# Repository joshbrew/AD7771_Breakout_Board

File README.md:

# AD7771_Breakout_Board
Unfinished AD7771 Breakout design. It works it's just not final.

The flex pieces were just unfinished thought experiments on a quick and dirty way to implement these AD7771 boards for FNIRS.

The board designs do work, but the Isolated DC-DC converter pin declarations in the schematics are backwards, found out the hard way so it is fixed in the design just not the footprint names in the .sch

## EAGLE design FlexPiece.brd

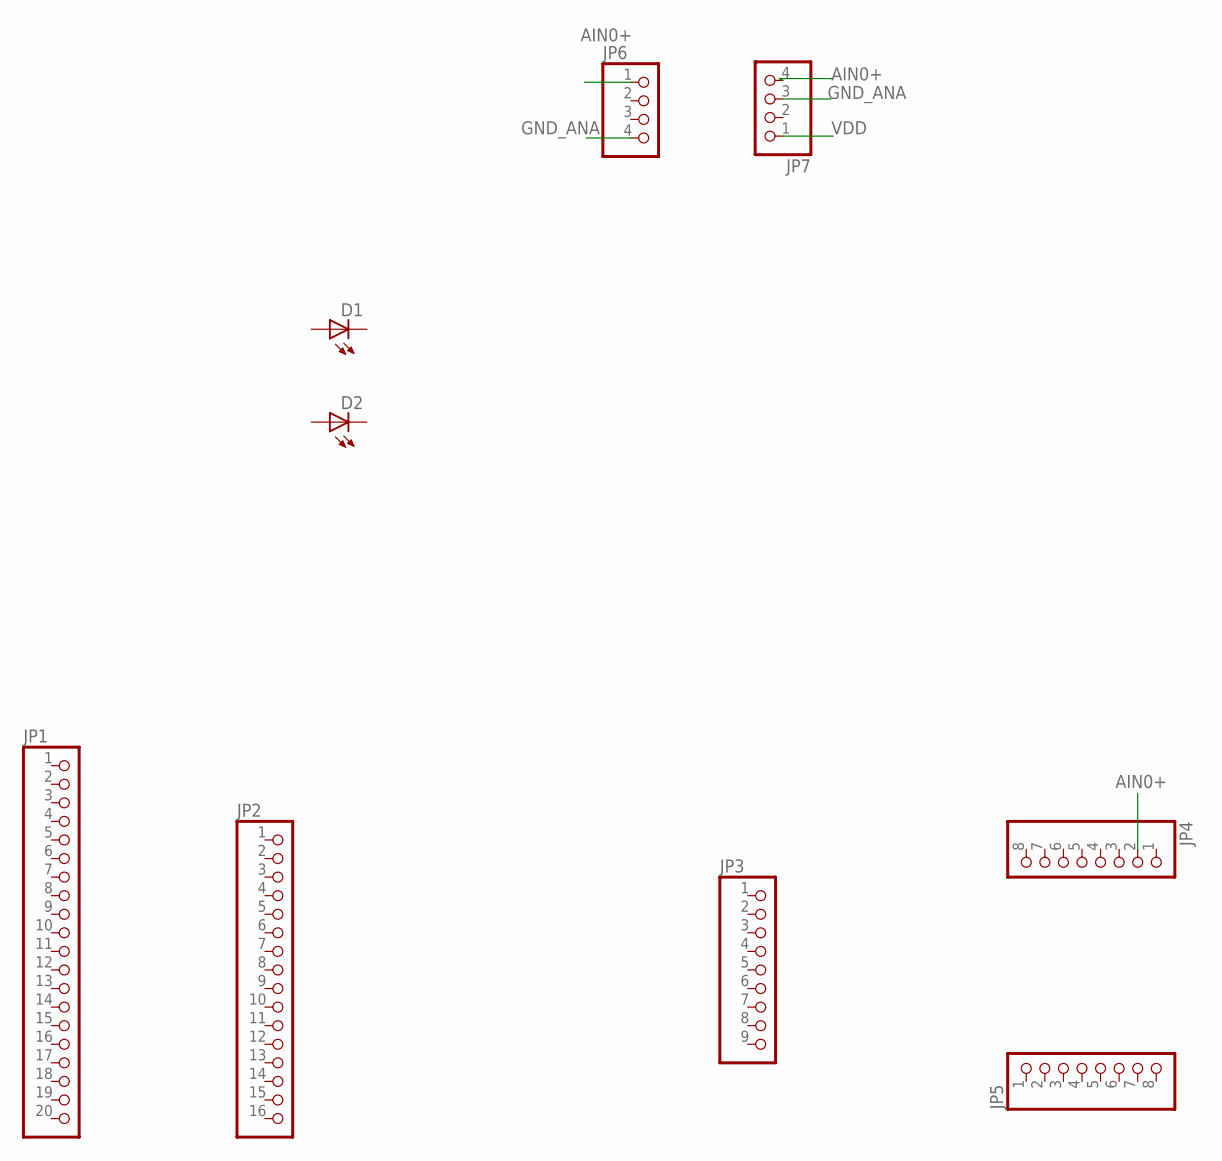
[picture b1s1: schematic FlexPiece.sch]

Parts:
D1, D2: LED1206; LED-1206
JP1: PINHD-1X20; 1X20
JP2: PINHD-1X16; 1X16
JP3: PINHD-1X9; 1X09
JP4, JP5: PINHD-1X8; 1X08
JP6, JP7: PINHD-1X4; 1X04

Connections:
AIN0+: JP4.2, JP6.1, JP7.4
GND_ANA: JP6.4, JP7.3
VDD: JP7.1

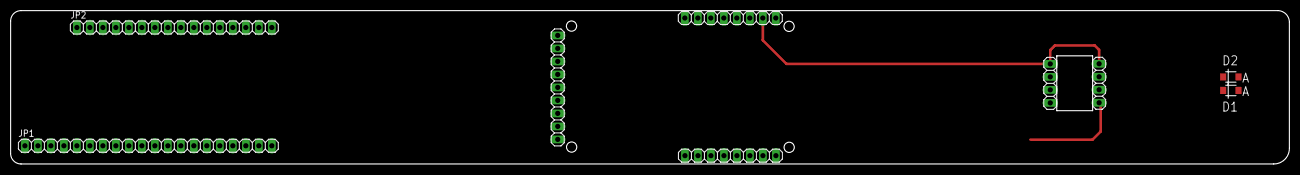
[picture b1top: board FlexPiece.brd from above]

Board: 2 copper layers, 249.9 x 30.0 mm, 9 parts (0 on the bottom side), 2 nets.

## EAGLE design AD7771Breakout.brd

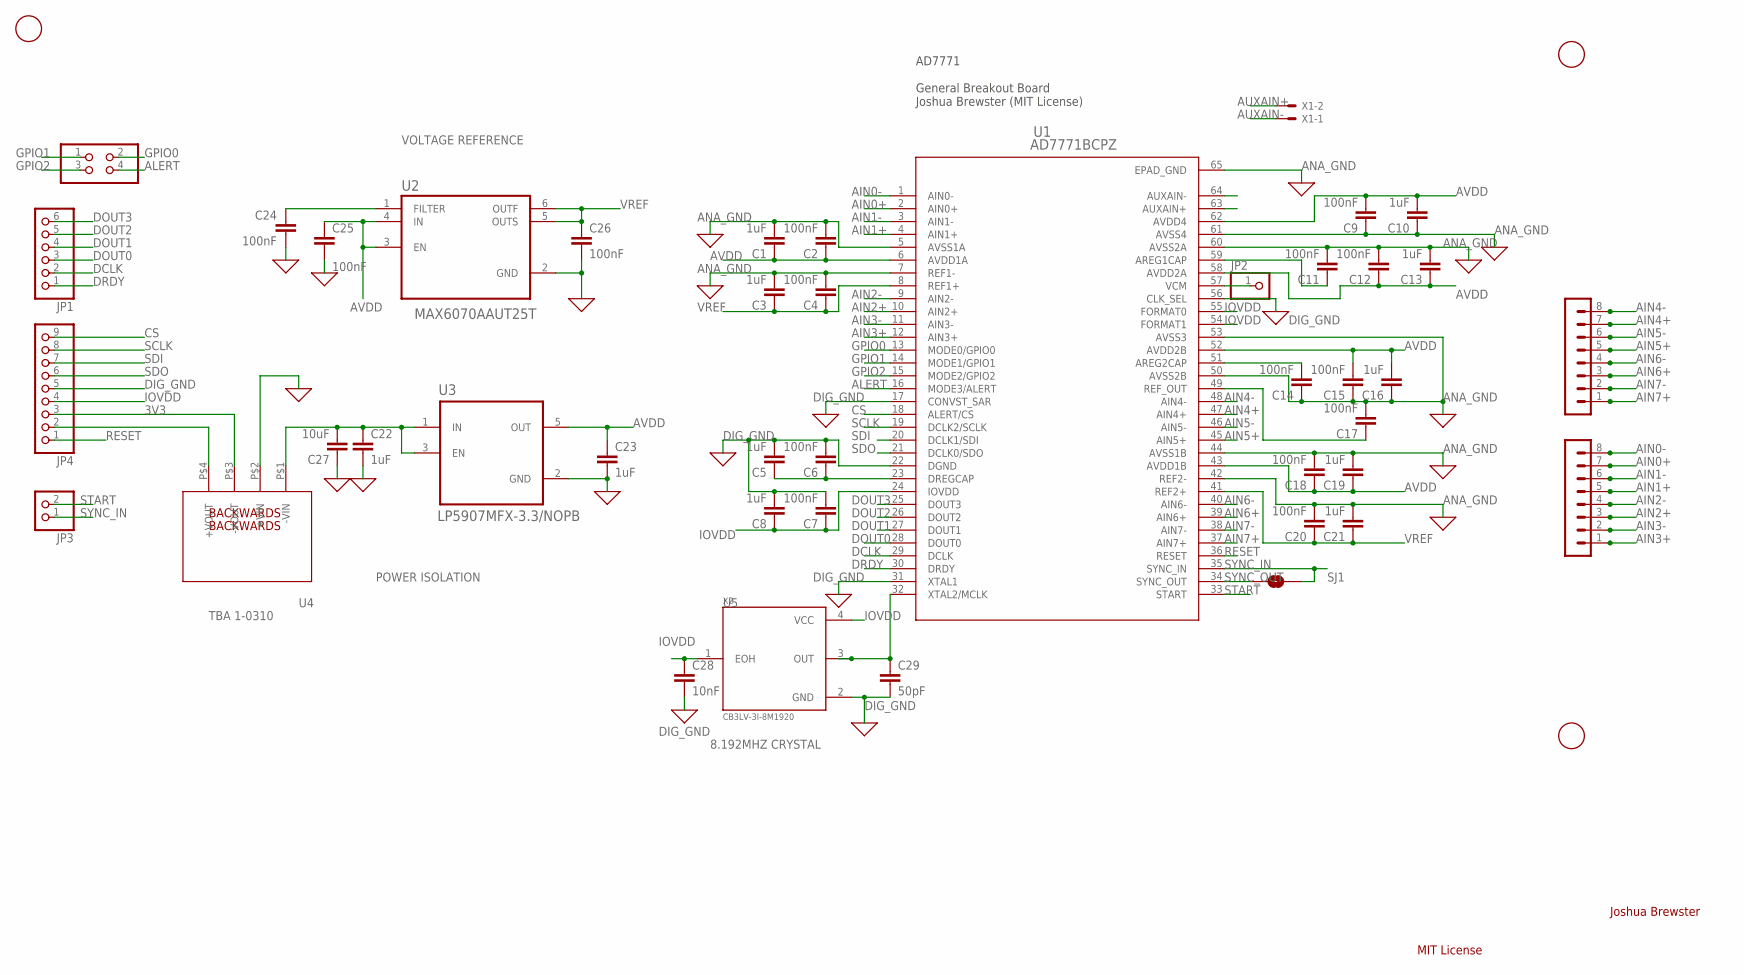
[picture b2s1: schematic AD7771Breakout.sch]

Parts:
C1, C3, C5, C8, C10, C13, C16, C19, C21, C22, C23: 1uF; C0402
C2, C4, C6, C7, C9, C11, C12, C14, C15, C17, C18, C20, C24, C25, C26: 100nF; C0402
C27: 10uF; C0402
C28: 10nF; C0402
C29: 50pF; C0603
JP1: PINHD-1X6; 1X06
JP2: PINHD-1X1; 1X01
JP3: PINHD-1X2; 1X02
JP4: PINHD-1X9; 1X09
JP5: PINHD-2X2; 2X02
SJ1: SOLDERJUMPERNC; SJ_2S_SMALL
SV4, SV5: MA08-1
U1: AD7771BCPZ; CP_64_15_ADI
U2: MAX6070AAUT25T; SOT95P280X145-6N
U3: LP5907MFX-3.3/NOPB; SOT95P280X145-5N
U4: TBA1-0310; SIP4-KT
U$1, U$2, U$5: FIDUCIAL; FIDUCIAL_1MM
X1: 332-02
X2: CB3LV-3I-8M1920; OSCCC700X500X180-4N

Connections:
3V3: JP4.3, U4.P$3 (-VOUT)
AGND_OUT: JP4.2, U4.P$4 (+VOUT)
AIN0+: SV4.7, U1.2 (AIN0+)
AIN0-: SV4.8, U1.1 (AIN0-)
AIN1+: SV4.5, U1.4 (AIN1+)
AIN1-: SV4.6, U1.3 (AIN1-)
AIN2+: SV4.3, U1.10 (AIN2+)
AIN2-: SV4.4, U1.9 (AIN2-)
AIN3+: SV4.1, U1.12 (AIN3+)
AIN3-: SV4.2, U1.11 (AIN3-)
AIN4+: SV5.7, U1.47 (AIN4+)
AIN4-: SV5.8, U1.48 (AIN4-)
AIN5+: SV5.5, U1.45 (AIN5+)
AIN5-: SV5.6, U1.46 (AIN5-)
AIN6+: SV5.3, U1.39 (AIN6+)
AIN6-: SV5.4, U1.40 (AIN6-)
AIN7+: SV5.1, U1.37 (AIN7+)
AIN7-: SV5.2, U1.38 (AIN7-)
ALERT: JP5.4, U1.16 (MODE3/ALERT)
ANA_GND: C1.2, C2.2, C3.2, C4.2, C9.1, C10.1, C11.2, C12.2, C13.2, C14.1, C15.1, C16.1, C17.2, C18.2, C19.2, C20.2, C21.2, C22.2, C23.2, C24.2, C25.2, C26.2, C27.1, U1.5 (AVSS1A), U1.7 (REF1-), U1.42 (REF2-), U1.44 (AVSS1B), U1.50 (AVSS2B), U1.53 (AVSS3), U1.60 (AVSS2A), U1.61 (AVSS4), U1.65 (EPAD_GND), U2.2 (GND), U3.2 (GND), U4.P$2 (+VIN)
AREG1CAP: C11.1, U1.59 (AREG1CAP)
AREG2CAP: C14.2, U1.51 (AREG2CAP)
AUXAIN+: U1.63 (AUXAIN+), X1.2
AUXAIN-: U1.64 (AUXAIN-), X1.1
AVDD: C1.1, C2.1, C9.2, C10.2, C12.1, C13.1, C15.2, C16.2, C18.1, C19.1, C23.1, C25.1, U1.6 (AVDD1A), U1.43 (AVDD1B), U1.52 (AVDD2B), U1.58 (AVDD2A), U1.62 (AVDD4), U2.3 (EN), U2.4 (IN), U3.5 (OUT)
CS: JP4.9, U1.18 (ALERT/CS)
DCLK: JP1.2, U1.29 (DCLK)
DIG_GND: C5.2, C6.2, C7.2, C8.2, C28.2, C29.2, JP4.5, U1.17 (CONVST_SAR), U1.22 (DGND), U1.31 (XTAL1), U1.56 (CLK_SEL), X2.2 (GND)
DOUT0: JP1.3, U1.28 (DOUT0)
DOUT1: JP1.4, U1.27 (DOUT1)
DOUT2: JP1.5, U1.26 (DOUT2)
DOUT3: JP1.6, U1.25 (DOUT3)
DRDY: JP1.1, U1.30 (DRDY)
DREGCAP: C5.1, C6.1, U1.23 (DREGCAP)
FILTER: C24.1, U2.1 (FILTER)
GPIO0: JP5.2, U1.13 (MODE0/GPIO0)
GPIO1: JP5.1, U1.14 (MODE1/GPIO1)
GPIO2: JP5.3, U1.15 (MODE2/GPIO2)
IOVDD: C7.1, C8.1, C28.1, JP4.4, U1.24 (IOVDD), U1.54 (FORMAT1), U1.55 (FORMAT0), X2.1 (EOH), X2.4 (VCC)
REF_OUT: C17.1, U1.49 (REF_OUT)
RESET: JP4.1, U1.36 (RESET)
SCLK: JP4.8, U1.19 (DCLK2/SCLK)
SDI: JP4.7, U1.20 (DCLK1/SDI)
SDO: JP4.6, U1.21 (DCLK0/SDO)
START: JP3.2, U1.33 (START)
SYNC_IN: JP3.1, SJ1.2, U1.35 (SYNC_IN)
SYNC_OUT: SJ1.1, U1.34 (SYNC_OUT)
VCM: JP2.1, U1.57 (VCM)
VOUT+: C22.1, C27.2, U3.1 (IN), U3.3 (EN), U4.P$1 (-VIN)
VREF: C3.1, C4.1, C20.1, C21.1, C26.1, U1.8 (REF1+), U1.41 (REF2+), U2.5 (OUTS), U2.6 (OUTF)
XTAL2: C29.1, U1.32 (XTAL2/MCLK), X2.3 (OUT)

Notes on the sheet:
AD7771 General Breakout Board Joshua Brewster (MIT License)
TBA 1-0310
POWER ISOLATION
VOLTAGE REFERENCE
8.192MHZ CRYSTAL
Joshua Brewster
MIT License
BACKWARDS

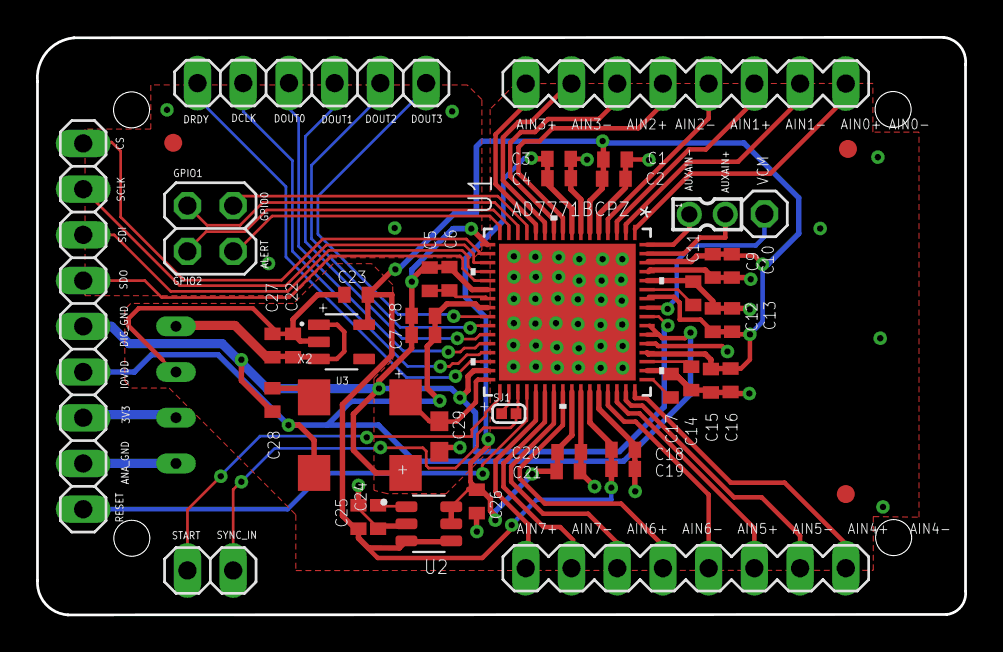
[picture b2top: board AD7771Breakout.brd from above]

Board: 2 copper layers, 51.6 x 32.1 mm, 46 parts (1 on the bottom side), 51 nets.

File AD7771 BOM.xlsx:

Designation | Qty | Package | Value | Part # | Mouser Prices (high) | 1.0 | 10.0 | 100.0 | 1000.0 | Link
U1 | 1.0 |  |  | AD7771BCPZ | 584-AD7771BCPZ | 18.23 | 167.5 | 1345.0 | 11360.0 | https://www.mouser.com/ProductDetail/Analog-Devices/AD7771BC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
U2 | 1.0 |  |  | MAX6070AAUT25T | 700-MAX6070AAUT25+T | 2.63 | 23.6 | 183.0 | 1600.0 | https://www.mouser.com/ProductDetail/Maxim-Integrated/MAX607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
U3 | 1.0 |  |  | LP5907MFX-3.3/NOPB | 595-LP5907MFX-3.3NPB | 0.55 | 4.31 | 32.0 | 191.0 | https://www.mouser.com/ProductDetail/Texas-Instruments/LP590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
U4 | 1.0 |  |  | TBA 1-0310 | 495-TBA1-0310 | 3.24 | 31.7 | 280.0 | 2430.0 | https://www.mouser.com/ProductDetail/TRACO-Power/TBA-1-0310?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
U5 | 1.0 |  |  | SG-210STF8.1920ML3 | 732-SG210STF8.1920L3 | 1.18 | 10.9 | 93.3 | 764.0 | https://www.mouser.com/ProductDetail/Epson-Timing/SG-210STF-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
C1, C3, C5, C8, C10, C13, C16, C19, C21, C22, C23 | 11.0 | C0402 | 1uF |  | 963-JMK105BJ105KP-F | 1.1 | 4.95 | 35.2 | 275 | https://www.mouser.com/ProductDetail/Taiyo-Yuden/JMK105BJ105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
C2, C4, C6, C7, C9, C11, C12, C14, C15, C17, C18, C20, C24, C25, C26 | 14.0 | C0402 | 100nF |  | 963-LMF105B7104KVHF | 1.4 | 4.2 | 28 | 182 | https://www.mouser.com/ProductDetail/Taiyo-Yuden/LMF105B7104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
C27 | 1.0 | C0402 | 10uF |  | 963-JMK105CBJ106MV-F | 0.22 | 1.02 | 8.0 | 51.0
 |  |  |  | via PCBway: | PCB Estimate (lead-free) | 18.0 | 18.0 | 50.0 | 235.0 | HASL lead free, 27mmX46.5mm, 2mm thick, any finish
 |  |  |  |  | Assembly Estimate | 88.0 | 88.0 | 232.0 | 520.0
 |  |  |  |  | Totals | 134.55 | 354.18 | 2286.5 | 17608
 |  |  |  | Additional Flex Piece Parts
 |  |  |  | OPT 101 |  | 0.9 | 9.0 | 90.0 | 900.0 | Aliexpress estimate
 |  |  |  | BR1102W |  | 0.5 | 3.09 | 14.2 | 119.0 | https://www.mouser.com/ProductDetail/Stanley-Electric/BR1102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
 |  |  |  | HAN1102W |  | 0.38 | 2.5 | 16.1 | 126.0 | https://www.mouser.com/ProductDetail/Stanley-Electric/HAN110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
 |  |  |  | LOLIN32 |  | 4.0 | 40.0 | 400.0 | 4000.0 | Aliexpress estimate
 |  |  |  |  | Flex board by PCBway | 131.0 | 152.0 | 375.0 | 2336.0 | 250mmX30mm, 0.23mm thickness, 0.7mm thick FR4 stiffener (boths sides for manual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
 |  |  |  |  | Extended Totals | 271.33 | 560.77 | 3181.8 | 25089
 |  |  |  | Other
 |  |  |  | Batteries | 300mAh-500mAh
 |  |  |  | Headband | Neoprene + plastic casing, something for the flex part.
 |  |  |  | Labor | Assembling the whole thing, testing, and packaging (done in-house)
